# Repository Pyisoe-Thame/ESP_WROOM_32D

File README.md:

# ESP-WROOM-32D

This repository contains files and designs created while following a YouTube tutorial on KiCad. 
The ESP-WROOM-32D is the same chip used in NodeMCU-32S development board. 
So, it is good to have touched this module in a learning curve.

## Original Tutorial

The designs in this project are based on the tutorial available at the following link: </br>
<a align="center" href="https://www.youtube.com/watch?v=b-7bMl6fJio"> YouTube Tutorial </a>

## Disclaimer

The final PCB design in the project is the result of a learning endevor and neither tested practically nor optimized for production use.
Users must do double-check on designs, components, and connections for safety and functionality.
Afterall the main  purpose of this project is for the same-interest fellows to observe, make comments and elaborate ideas or collaborate into their own projects. 

## License

This project is dedicated to the public domain under the **Unlicense**. You can do whatever you want with it, including modifying, distributing, and using it for any purpose, without restriction. 

See the [Unlicense](http://unlicense.org/) for more details.

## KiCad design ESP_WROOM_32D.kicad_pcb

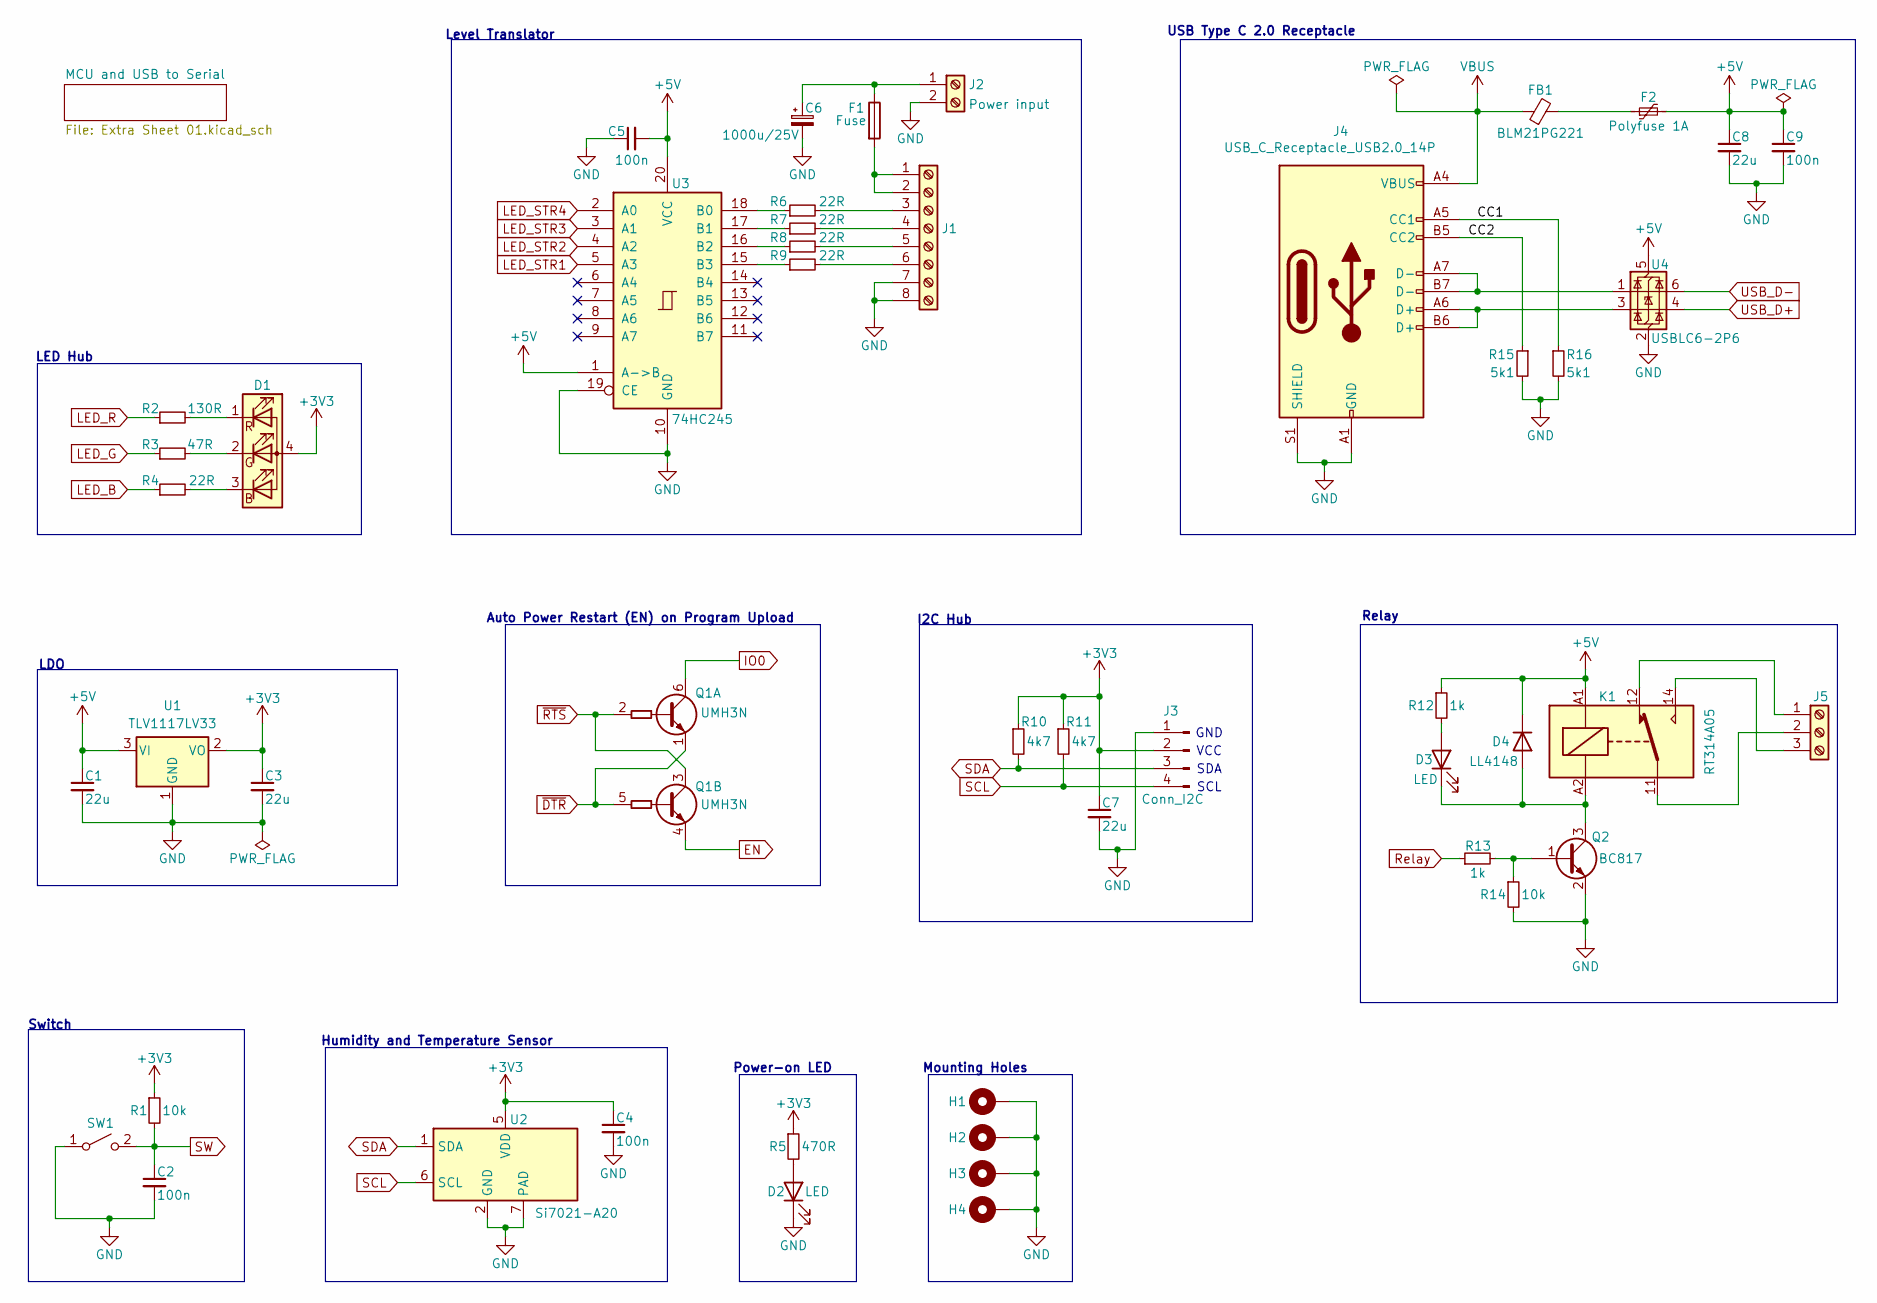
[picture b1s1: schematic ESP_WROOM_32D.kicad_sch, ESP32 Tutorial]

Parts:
C1, C3, C7, C8: 22u; C_0805_2012Metric_Pad1.18x1.45mm_HandSolder
C2, C4, C5, C9: 100n; C_0402_1005Metric_Pad0.74x0.62mm_HandSolder
C6: 1000u/25V; CP_Radial_D10.0mm_P5.00mm
D1: LED_RGBA; LED_RGB_Wuerth-PLCC4_3.2x2.8mm_150141M173100
D2, D3: LED; LED_0603_1608Metric_Pad1.05x0.95mm_HandSolder
D4: LL4148; D_MiniMELF
F1: Fuse; Fuseholder_Clip-5x20mm_Keystone_3517_Inline_P23.11x6.76mm_D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
F2: Polyfuse 1A; Fuse_0805_2012Metric_Pad1.15x1.40mm_HandSolder
FB1: BLM21PG221; L_0603_1608Metric
H1, H2, H3, H4: MountingHole_Pad; MountingHole_3.2mm_M3_Pad
J1: Screw_Terminal_01x08; TerminalBlock_Phoenix_MKDS-1,5-8-5.08_1x08_P5.08mm_Horizont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
J2: Power input; TerminalBlock_Phoenix_MKDS-1,5-2-5.08_1x02_P5.08mm_Horizont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
J3: Conn_I2C; PinHeader_1x04_P2.54mm_Vertical
J4: USB_C_Receptacle_USB2.0_14P; USB_C_Receptacle_HRO_TYPE-C-31-M-12
J5: Screw_Terminal_01x03; TerminalBlock_Phoenix_MKDS-1,5-3-5.08_1x03_P5.08mm_Horizont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
K1: RT314A05; Relay_SPDT_Schrack-RT1-16A-FormC_RM5mm
Q1: UMH3N; SOT-363_SC-70-6
Q2: BC817; SOT-23
R1, R14: 10k; R_0402_1005Metric_Pad0.72x0.64mm_HandSolder
R2: 130R; R_0402_1005Metric_Pad0.72x0.64mm_HandSolder
R3: 47R; R_0402_1005Metric_Pad0.72x0.64mm_HandSolder
R4, R6, R7, R8, R9: 22R; R_0402_1005Metric_Pad0.72x0.64mm_HandSolder
R5: 470R; R_0402_1005Metric_Pad0.72x0.64mm_HandSolder
R10, R11: 4k7; R_0402_1005Metric_Pad0.72x0.64mm_HandSolder
R12, R13: 1k; R_0402_1005Metric_Pad0.72x0.64mm_HandSolder
R15, R16: 5k1; R_0402_1005Metric_Pad0.72x0.64mm_HandSolder
SW1: SW_SPST; SW_DIP_SPSTx01_Slide_6.7x4.1mm_W6.73mm_P2.54mm_LowProfile_J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
U1: TLV1117LV33; SOT-223-3_TabPin2
U2: Si7021-A20; DFN-6-1EP_3x3mm_P1mm_EP1.5x2.4mm
U3: 74HC245; DIP-20_W7.62mm_Socket_LongPads
U4: USBLC6-2P6; SOT-666

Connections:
+3V3: C3.1, C4.1, C7.1, D1.4 (A), J3.2, R1.1, R5.1, R10.1, R11.1, U1.2 (VO), U2.5 (VDD); also elsewhere on the board
+5V: C1.1, C5.2, C8.1, C9.1, D4.1 (K), F2.2, K1.A1, R12.1, U1.3 (VI), U3.1 (A->B), U3.20 (VCC), U4.5 (VBUS); also elsewhere on the board
/CC1: J4.A5 (CC1), R16.1
/CC2: J4.B5 (CC2), R15.1
EN: Q1.4 (E2); also elsewhere on the board
GND: C1.2, C2.2, C3.2, C4.2, C5.1, C6.2, C7.2, C8.2, C9.2, D2.1 (K), H1.1, H2.1, H3.1, H4.1, J1.7, J1.8, J2.2, J3.1, J4.A1 (GND), J4.A12 (GND), J4.B1 (GND), J4.B12 (GND), J4.S1 (SHIELD), Q2.2 (E), R14.2, R15.2, R16.2, SW1.1 (A), U1.1 (GND), U2.2 (GND), U2.7 (PAD), U3.10 (GND), U3.19 (CE), U4.2 (GND); also elsewhere on the board
IO0: Q1.6 (C1); also elsewhere on the board
LED_B: R4.1; also elsewhere on the board
LED_G: R3.1; also elsewhere on the board
LED_R: R2.1; also elsewhere on the board
LED_STR1: U3.5 (A3); also elsewhere on the board
LED_STR2: U3.4 (A2); also elsewhere on the board
LED_STR3: U3.3 (A1); also elsewhere on the board
LED_STR4: U3.2 (A0); also elsewhere on the board
unnamed: D1.3 (BK), R4.2
unnamed: D1.2 (GK), R3.2
unnamed: D1.1 (RK), R2.2
unnamed: D2.2 (A), R5.2
unnamed: D3.2 (A), R12.2
unnamed: D3.1 (K), D4.2 (A), K1.A2, Q2.3 (C)
unnamed: F2.1, FB1.2
unnamed: F1.2, J1.1, J1.2
unnamed: J1.3, R6.2
unnamed: J1.4, R7.2
unnamed: J1.5, R8.2
unnamed: J1.6, R9.2
unnamed: C6.1, F1.1, J2.1
unnamed: J4.A6 (D+), J4.B6 (D+), U4.3 (I/O2)
unnamed: J4.A7 (D-), J4.B7 (D-), U4.1 (I/O1)
unnamed: J5.1, K1.12
unnamed: J5.2, K1.11
unnamed: J5.3, K1.14
unnamed: Q2.1 (B), R13.2, R14.1
unnamed: R6.1, U3.18 (B0)
unnamed: R7.1, U3.17 (B1)
unnamed: R8.1, U3.16 (B2)
unnamed: R9.1, U3.15 (B3)
Relay: R13.1; also elsewhere on the board
SCL: J3.4, R11.2, U2.6 (SCL); also elsewhere on the board
SDA: J3.3, R10.2, U2.1 (SDA); also elsewhere on the board
SW: C2.1, R1.2, SW1.2 (B); also elsewhere on the board
USB_D+: U4.4 (I/O2); also elsewhere on the board
USB_D-: U4.6 (I/O1); also elsewhere on the board
VBUS: FB1.1, J4.A4 (VBUS), J4.A9 (VBUS), J4.B4 (VBUS), J4.B9 (VBUS)
~DTR: Q1.1 (E1), Q1.5 (B2); also elsewhere on the board
~RTS: Q1.2 (B1), Q1.3 (C2); also elsewhere on the board

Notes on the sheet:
SCL
USB Type C 2.0 Receptacle
GND
VCC
I2C Hub
SDA
Switch
Auto Power Restart (EN) on Program Upload
LED Hub
Humidity and Temperature Sensor
Power-on LED
Level Translator
LDO
Relay
Mounting Holes

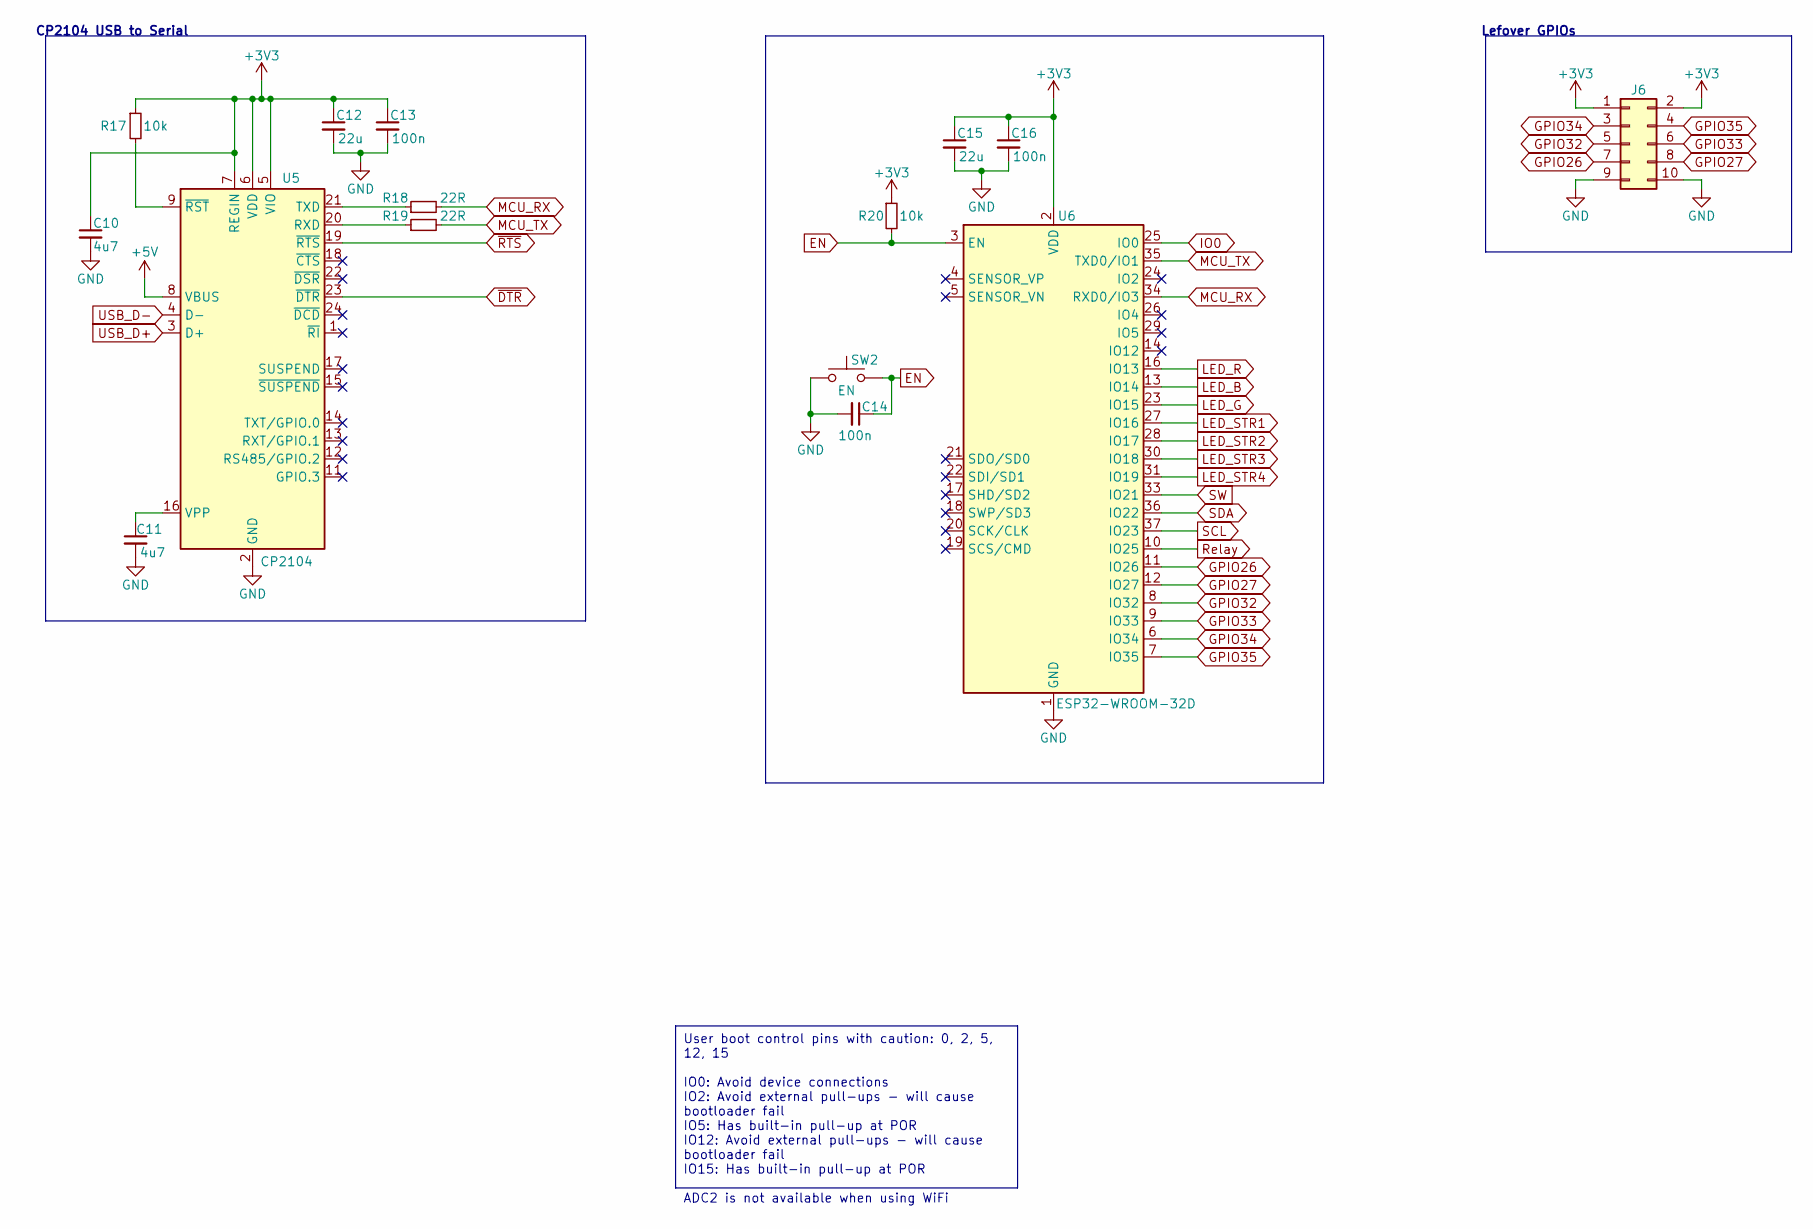
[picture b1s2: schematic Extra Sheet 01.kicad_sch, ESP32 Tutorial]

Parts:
C10, C11: 4u7; C_0805_2012Metric_Pad1.18x1.45mm_HandSolder
C12, C15: 22u; C_0805_2012Metric_Pad1.18x1.45mm_HandSolder
C13, C14, C16: 100n; C_0402_1005Metric_Pad0.74x0.62mm_HandSolder
J6: Conn_02x05_Odd_Even; PinHeader_2x05_P2.54mm_Vertical
R17, R20: 10k; R_0402_1005Metric_Pad0.72x0.64mm_HandSolder
R18, R19: 22R; R_0402_1005Metric_Pad0.72x0.64mm_HandSolder
SW2: EN; SW_PUSH_6mm
U5: CP2104; QFN-24-1EP_4x4mm_P0.5mm_EP2.6x2.6mm
U6: ESP32-WROOM-32D

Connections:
+3V3: C10.1, C12.1, C13.1, C15.1, C16.1, J6.1, J6.2, R17.1, R20.1, U5.5 (VIO), U5.6 (VDD), U5.7 (REGIN), U6.2 (VDD); also elsewhere on the board
+5V: U5.8 (VBUS); also elsewhere on the board
EN: C14.1, R20.2, SW2.1, U6.3 (EN); also elsewhere on the board
GND: C10.2, C11.2, C12.2, C13.2, C14.2, C15.2, C16.2, J6.9, J6.10, SW2.2, U5.2 (GND), U5.25 (GND), U6.1 (GND), U6.15 (GND), U6.38 (GND), U6.39 (GND); also elsewhere on the board
GPIO26: J6.7, U6.11 (IO26)
GPIO27: J6.8, U6.12 (IO27)
GPIO32: J6.5, U6.8 (IO32)
GPIO33: J6.6, U6.9 (IO33)
GPIO34: J6.3, U6.6 (IO34)
GPIO35: J6.4, U6.7 (IO35)
IO0: U6.25 (IO0); also elsewhere on the board
LED_B: U6.13 (IO14); also elsewhere on the board
LED_G: U6.23 (IO15); also elsewhere on the board
LED_R: U6.16 (IO13); also elsewhere on the board
LED_STR1: U6.27 (IO16); also elsewhere on the board
LED_STR2: U6.28 (IO17); also elsewhere on the board
LED_STR3: U6.30 (IO18); also elsewhere on the board
LED_STR4: U6.31 (IO19); also elsewhere on the board
MCU_RX: R18.2, U6.34 (RXD0/IO3)
MCU_TX: R19.2, U6.35 (TXD0/IO1)
unnamed: R19.1, U5.20 (RXD)
unnamed: R18.1, U5.21 (TXD)
unnamed: C11.1, U5.16 (VPP)
unnamed: R17.2, U5.9 (~RST)
Relay: U6.10 (IO25); also elsewhere on the board
SCL: U6.37 (IO23); also elsewhere on the board
SDA: U6.36 (IO22); also elsewhere on the board
SW: U6.33 (IO21); also elsewhere on the board
USB_D+: U5.3 (D+); also elsewhere on the board
USB_D-: U5.4 (D-); also elsewhere on the board
~DTR: U5.23 (~DTR); also elsewhere on the board
~RTS: U5.19 (~RTS); also elsewhere on the board

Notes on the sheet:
User boot control pins with caution: 0, 2, 5, 12, 15 IO0: Avoid device connections IO2: Avoid external pull-ups - will cause bootloader fail IO5: Has built-in pull-up at POR IO12: Avoid external pull-ups - will cause bootloader fail IO15: Has built-in pull-up at POR ADC2 is not available when using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
Lefover GPIOs
CP2104 USB to Serial

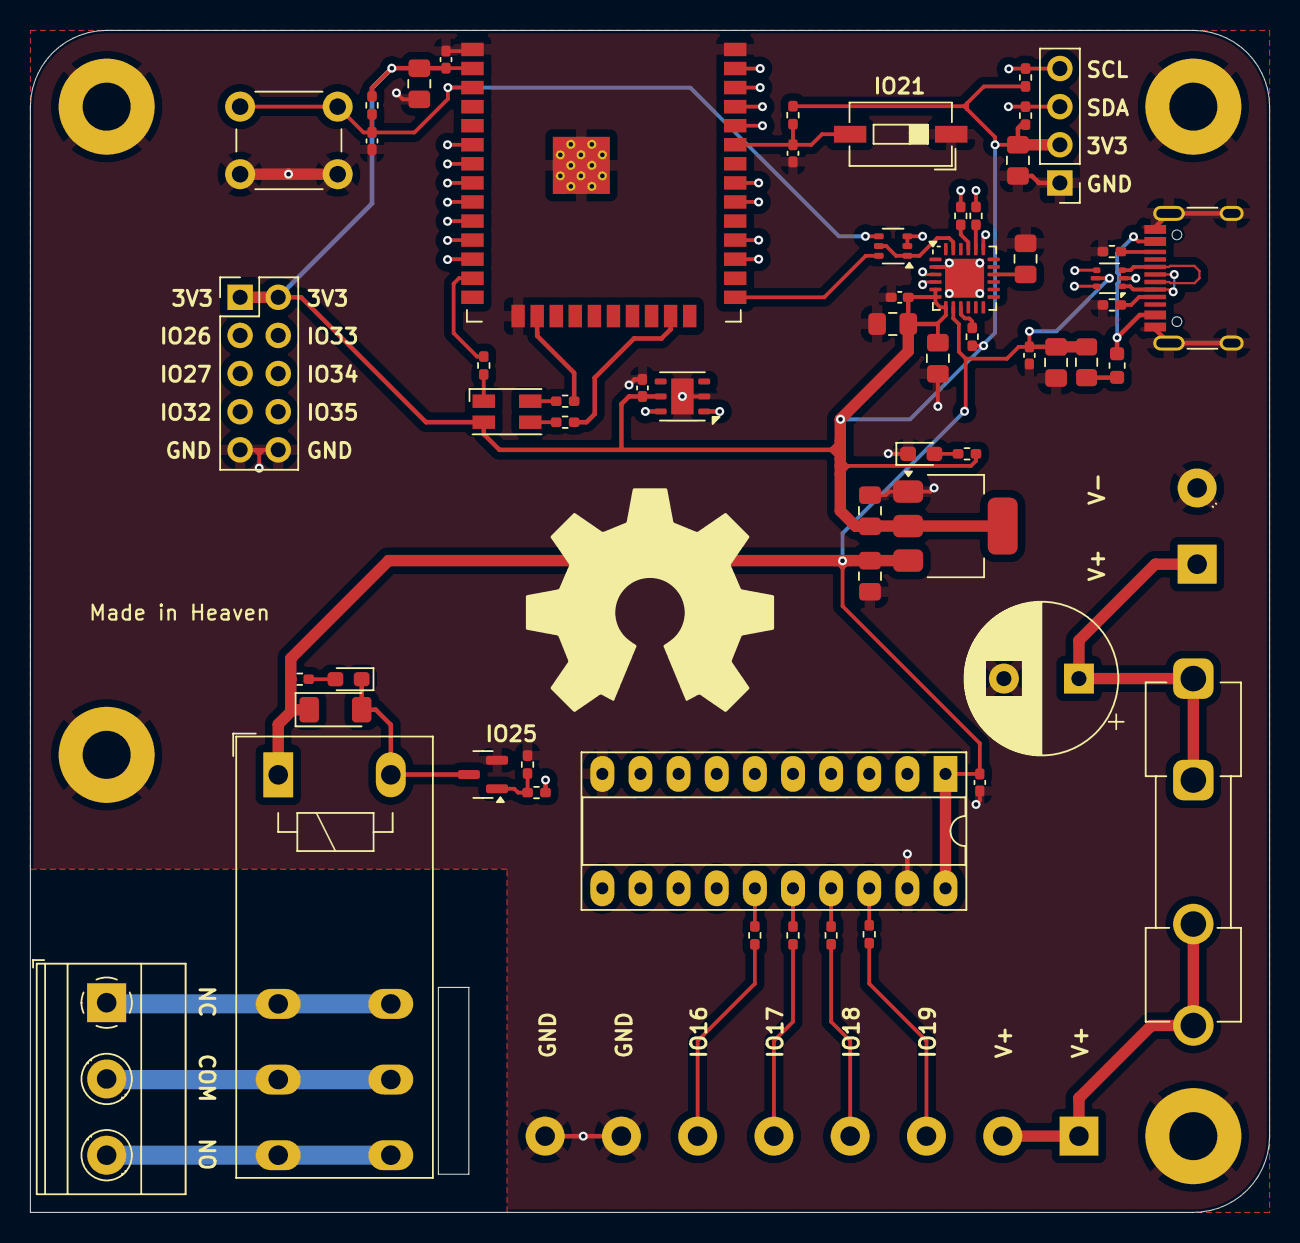
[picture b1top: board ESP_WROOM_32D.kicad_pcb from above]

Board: 4 copper layers, 82.5 x 78.7 mm, 64 parts (0 on the bottom side), 58 nets.

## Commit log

2024-12-31 initial_commit
